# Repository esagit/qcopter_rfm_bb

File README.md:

# Quadcopter - Breakout Board Adapter
Adafruit RFM9x LoRa &amp; Pmod NAV module Breakout Board for Arduino Mega 
* [Adafruit RFM9x LoRa](https://www.adafruit.com/product/3072)
* [Pmod NAV: 9-axis IMU Plus Barometer](http://store.digilentinc.com/pmod-nav-9-axis-imu-plus-barometer)

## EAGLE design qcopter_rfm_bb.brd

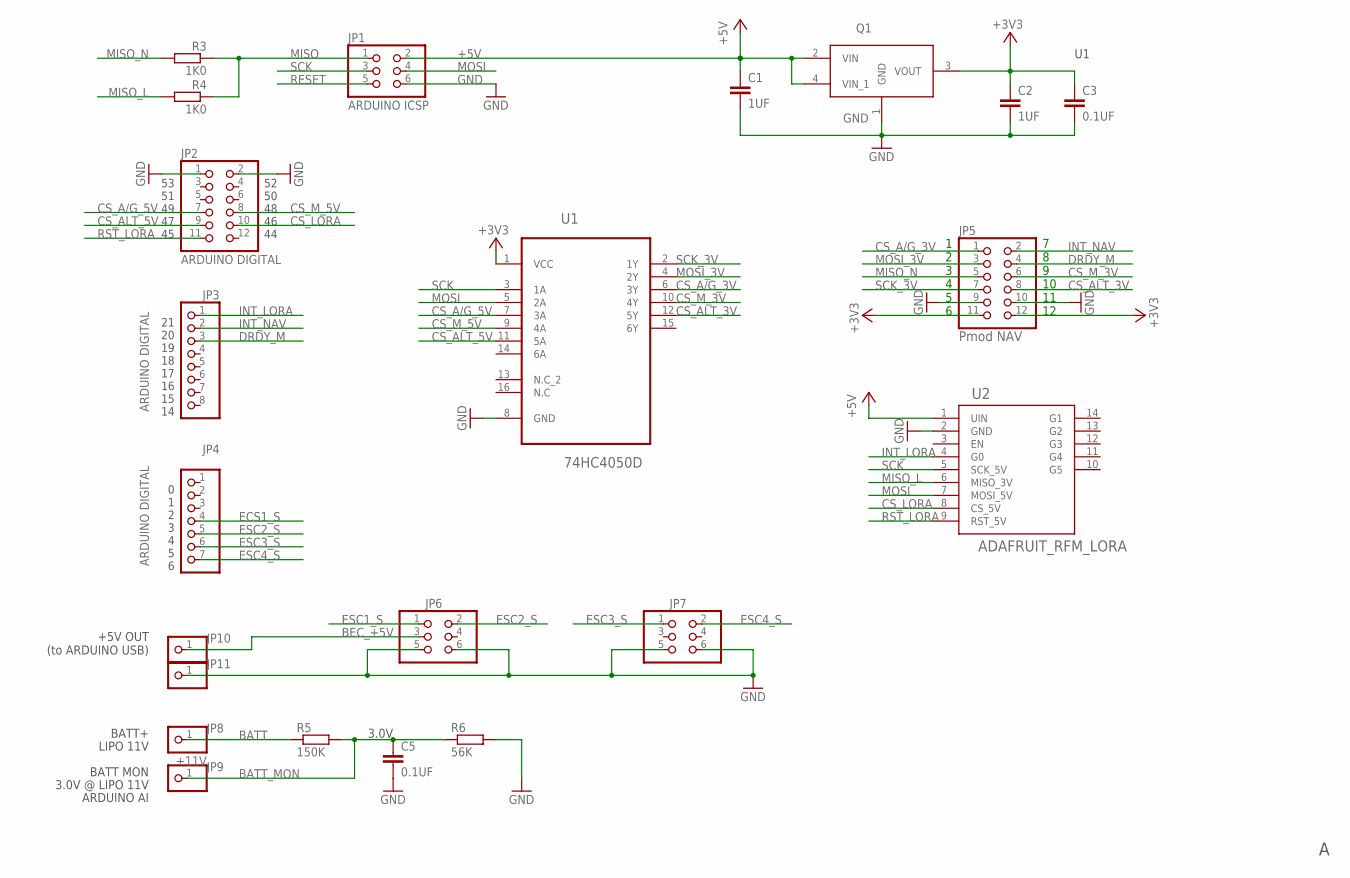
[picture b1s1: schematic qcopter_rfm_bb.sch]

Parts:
C1, C2: 1UF; C1206
C3, C5: 0.1UF; C1206
JP1: ARDUINO ICSP; 2X03
JP2: ARDUINO DIGITAL; 2X06
JP3: ARDUINO DIGITAL; 1X08
JP4: ARDUINO DIGITAL; 1X07
JP5: Pmod NAV; 2X06/90
JP6, JP7: PINHD-2X3; 2X03
JP8: +11V; 1X01
JP9, JP10, JP11: PINHD-1X1; 1X01
Q1: MCP17-MCP1703T-3302E/MB; SOT150P400X160-4N
R3, R4: 1K0; R1206
R5: 150K; R1206
R6: 56K; R1206
U1: 74HC4050D; SOIC127P600X175-16N
U2: ADAFRUIT_RFM_LORA; ADAFRUIT_RFM_LORA_B

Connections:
+3V3: C2.1, C3.1, JP5.11, JP5.12, Q1.3 (VOUT), U1.1 (VCC)
+5V: C1.1, JP1.2, Q1.2 (VIN), Q1.4 (VIN_1), U2.1 (UIN)
BATT: JP8.1, R5.1
BATT_MON: C5.1, JP9.1, R5.2, R6.1
BEC_+5V: JP6.3, JP10.1
CS_A/G_3V: JP5.1, U1.6 (3Y)
CS_A/G_5V: JP2.7, U1.7 (3A)
CS_ALT_3V: JP5.8, U1.12 (5Y)
CS_ALT_5V: JP2.9, U1.11 (5A)
CS_LORA: JP2.10, U2.8 (CS_5V)
CS_M_3V: JP5.6, U1.10 (4Y)
CS_M_5V: JP2.8, U1.9 (4A)
DRDY_M: JP3.3, JP5.4
ECS1_S: JP4.4
ESC1_S: JP6.1
ESC2_S: JP4.5, JP6.2
ESC3_S: JP4.6, JP7.1
ESC4_S: JP4.7, JP7.2
GND: C1.2, C2.2, C3.2, C5.2, JP1.6, JP2.1, JP2.2, JP5.9, JP5.10, JP6.5, JP6.6, JP7.5, JP7.6, JP11.1, Q1.1 (GND), R6.2, U1.8 (GND), U2.2 (GND)
INT_LORA: JP3.1, U2.4 (G0)
INT_NAV: JP3.2, JP5.2
MISO: JP1.1, R3.1, R4.1
MISO_L: R4.2, U2.6 (MISO_3V)
MISO_N: JP5.5, R3.2
MOSI: JP1.4, U1.5 (2A), U2.7 (MOSI_5V)
MOSI_3V: JP5.3, U1.4 (2Y)
RESET: JP1.5
RST_LORA: JP2.11, U2.9 (RST_5V)
SCK: JP1.3, U1.3 (1A), U2.5 (SCK_5V)
SCK_3V: JP5.7, U1.2 (1Y)

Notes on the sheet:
1 2 3 4 5 6
7 8 9 10 11 12
BATT+
BATT MON
3.0V @ LIPO 11V
3.0V
LIPO 11V
+5V OUT (to ARDUINO USB)
ARDUINO AI
21 20 19 18 17 16 15 14
0 1 2 3 4 5 6
53 51 49 47 45
52 50 48 46 44

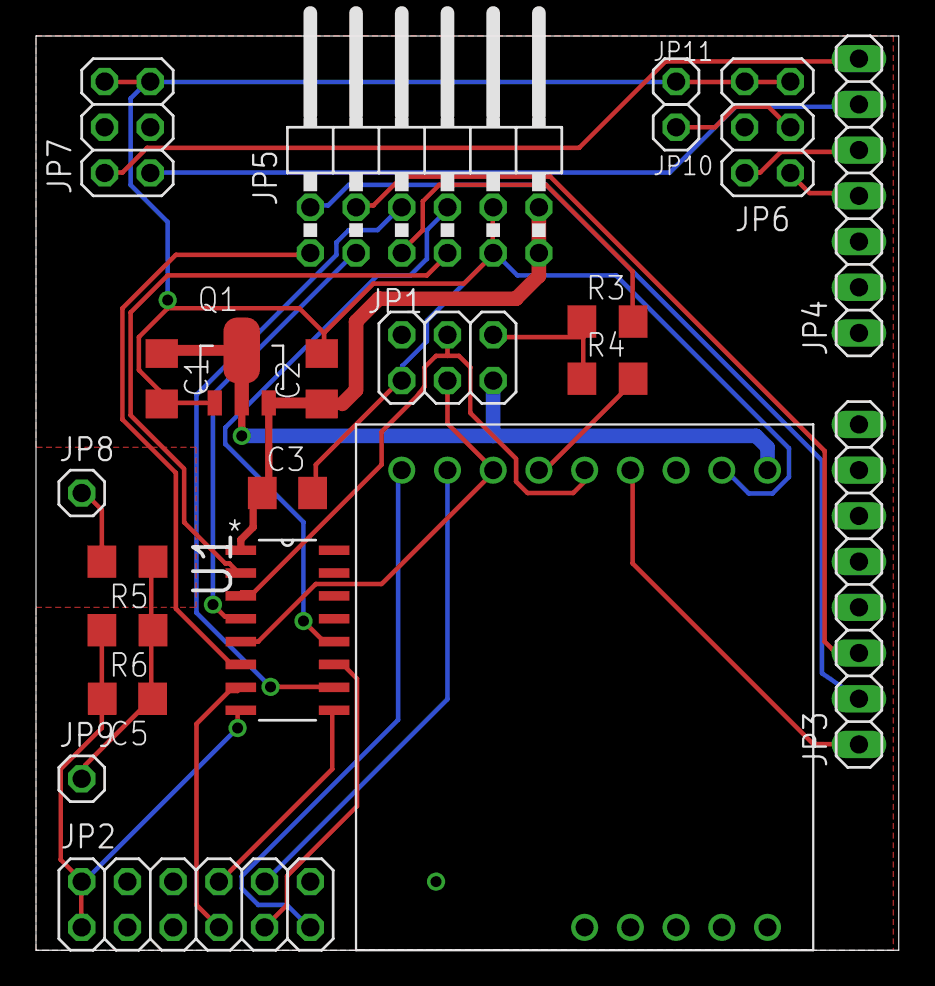
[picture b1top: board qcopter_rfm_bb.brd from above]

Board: 2 copper layers, 47.9 x 50.8 mm, 22 parts (0 on the bottom side), 27 nets.

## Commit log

2017-08-29 :circus_tent: Added .gitattributes & .gitignore files
2017-08-29 Initial commit
    Initial commit
